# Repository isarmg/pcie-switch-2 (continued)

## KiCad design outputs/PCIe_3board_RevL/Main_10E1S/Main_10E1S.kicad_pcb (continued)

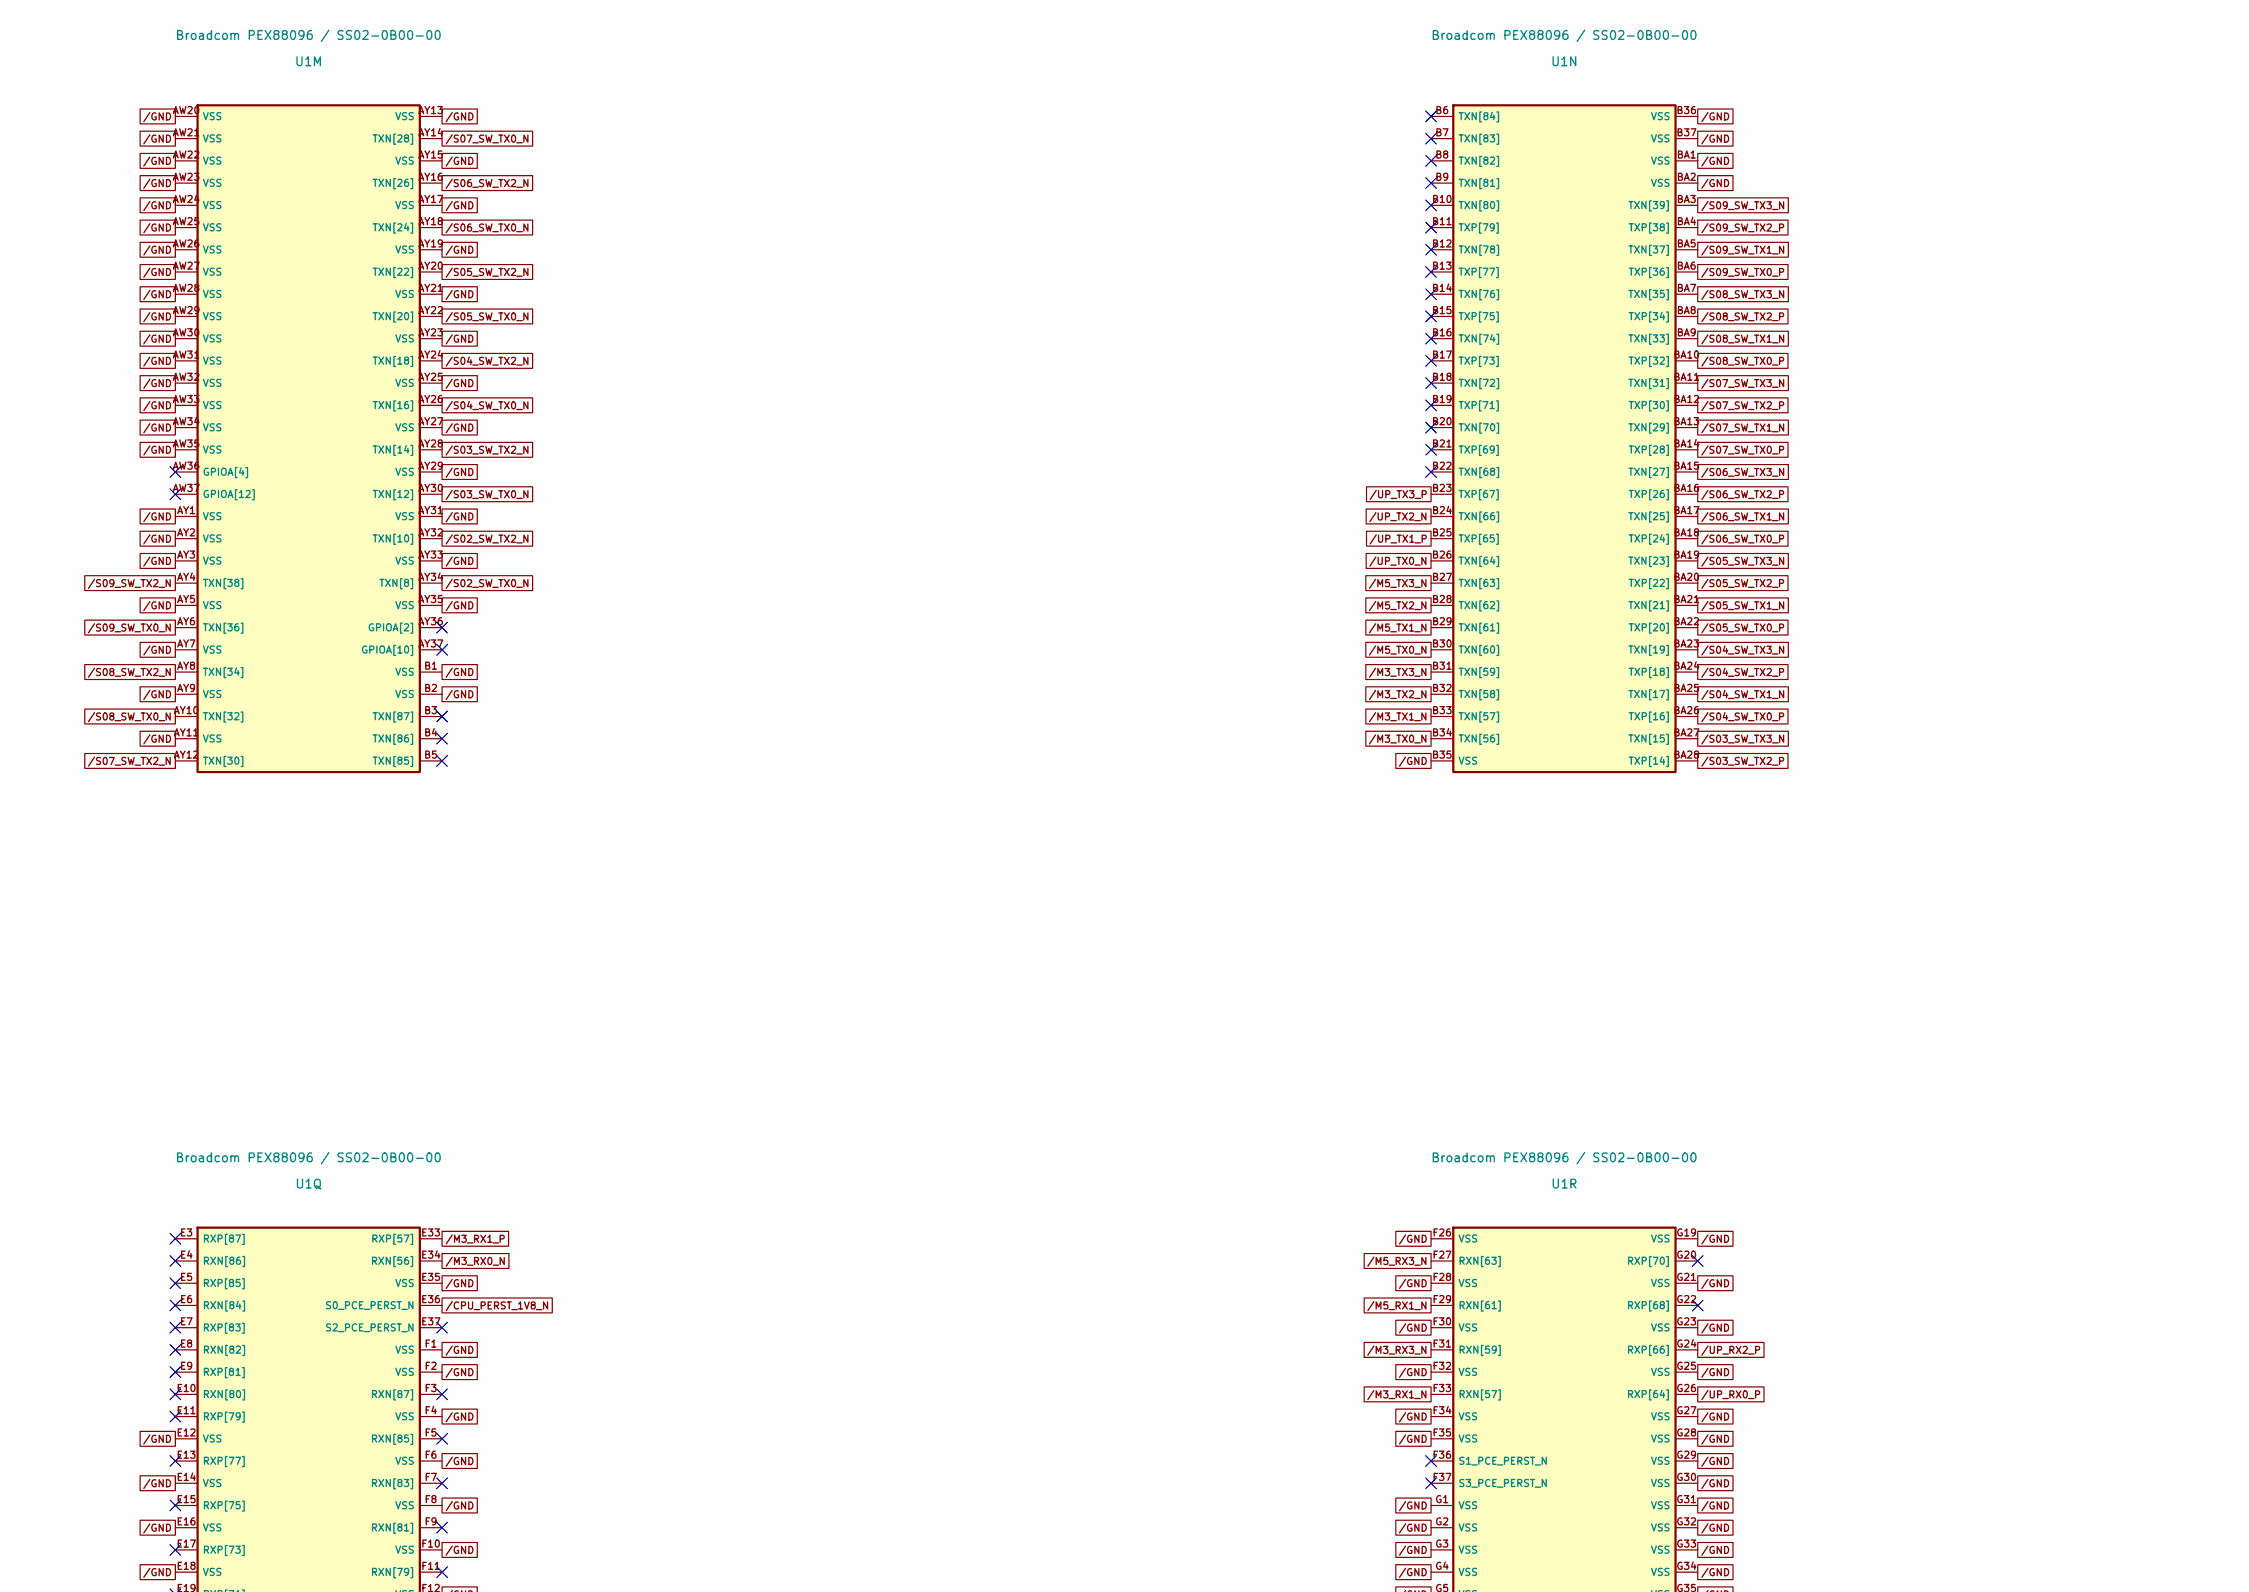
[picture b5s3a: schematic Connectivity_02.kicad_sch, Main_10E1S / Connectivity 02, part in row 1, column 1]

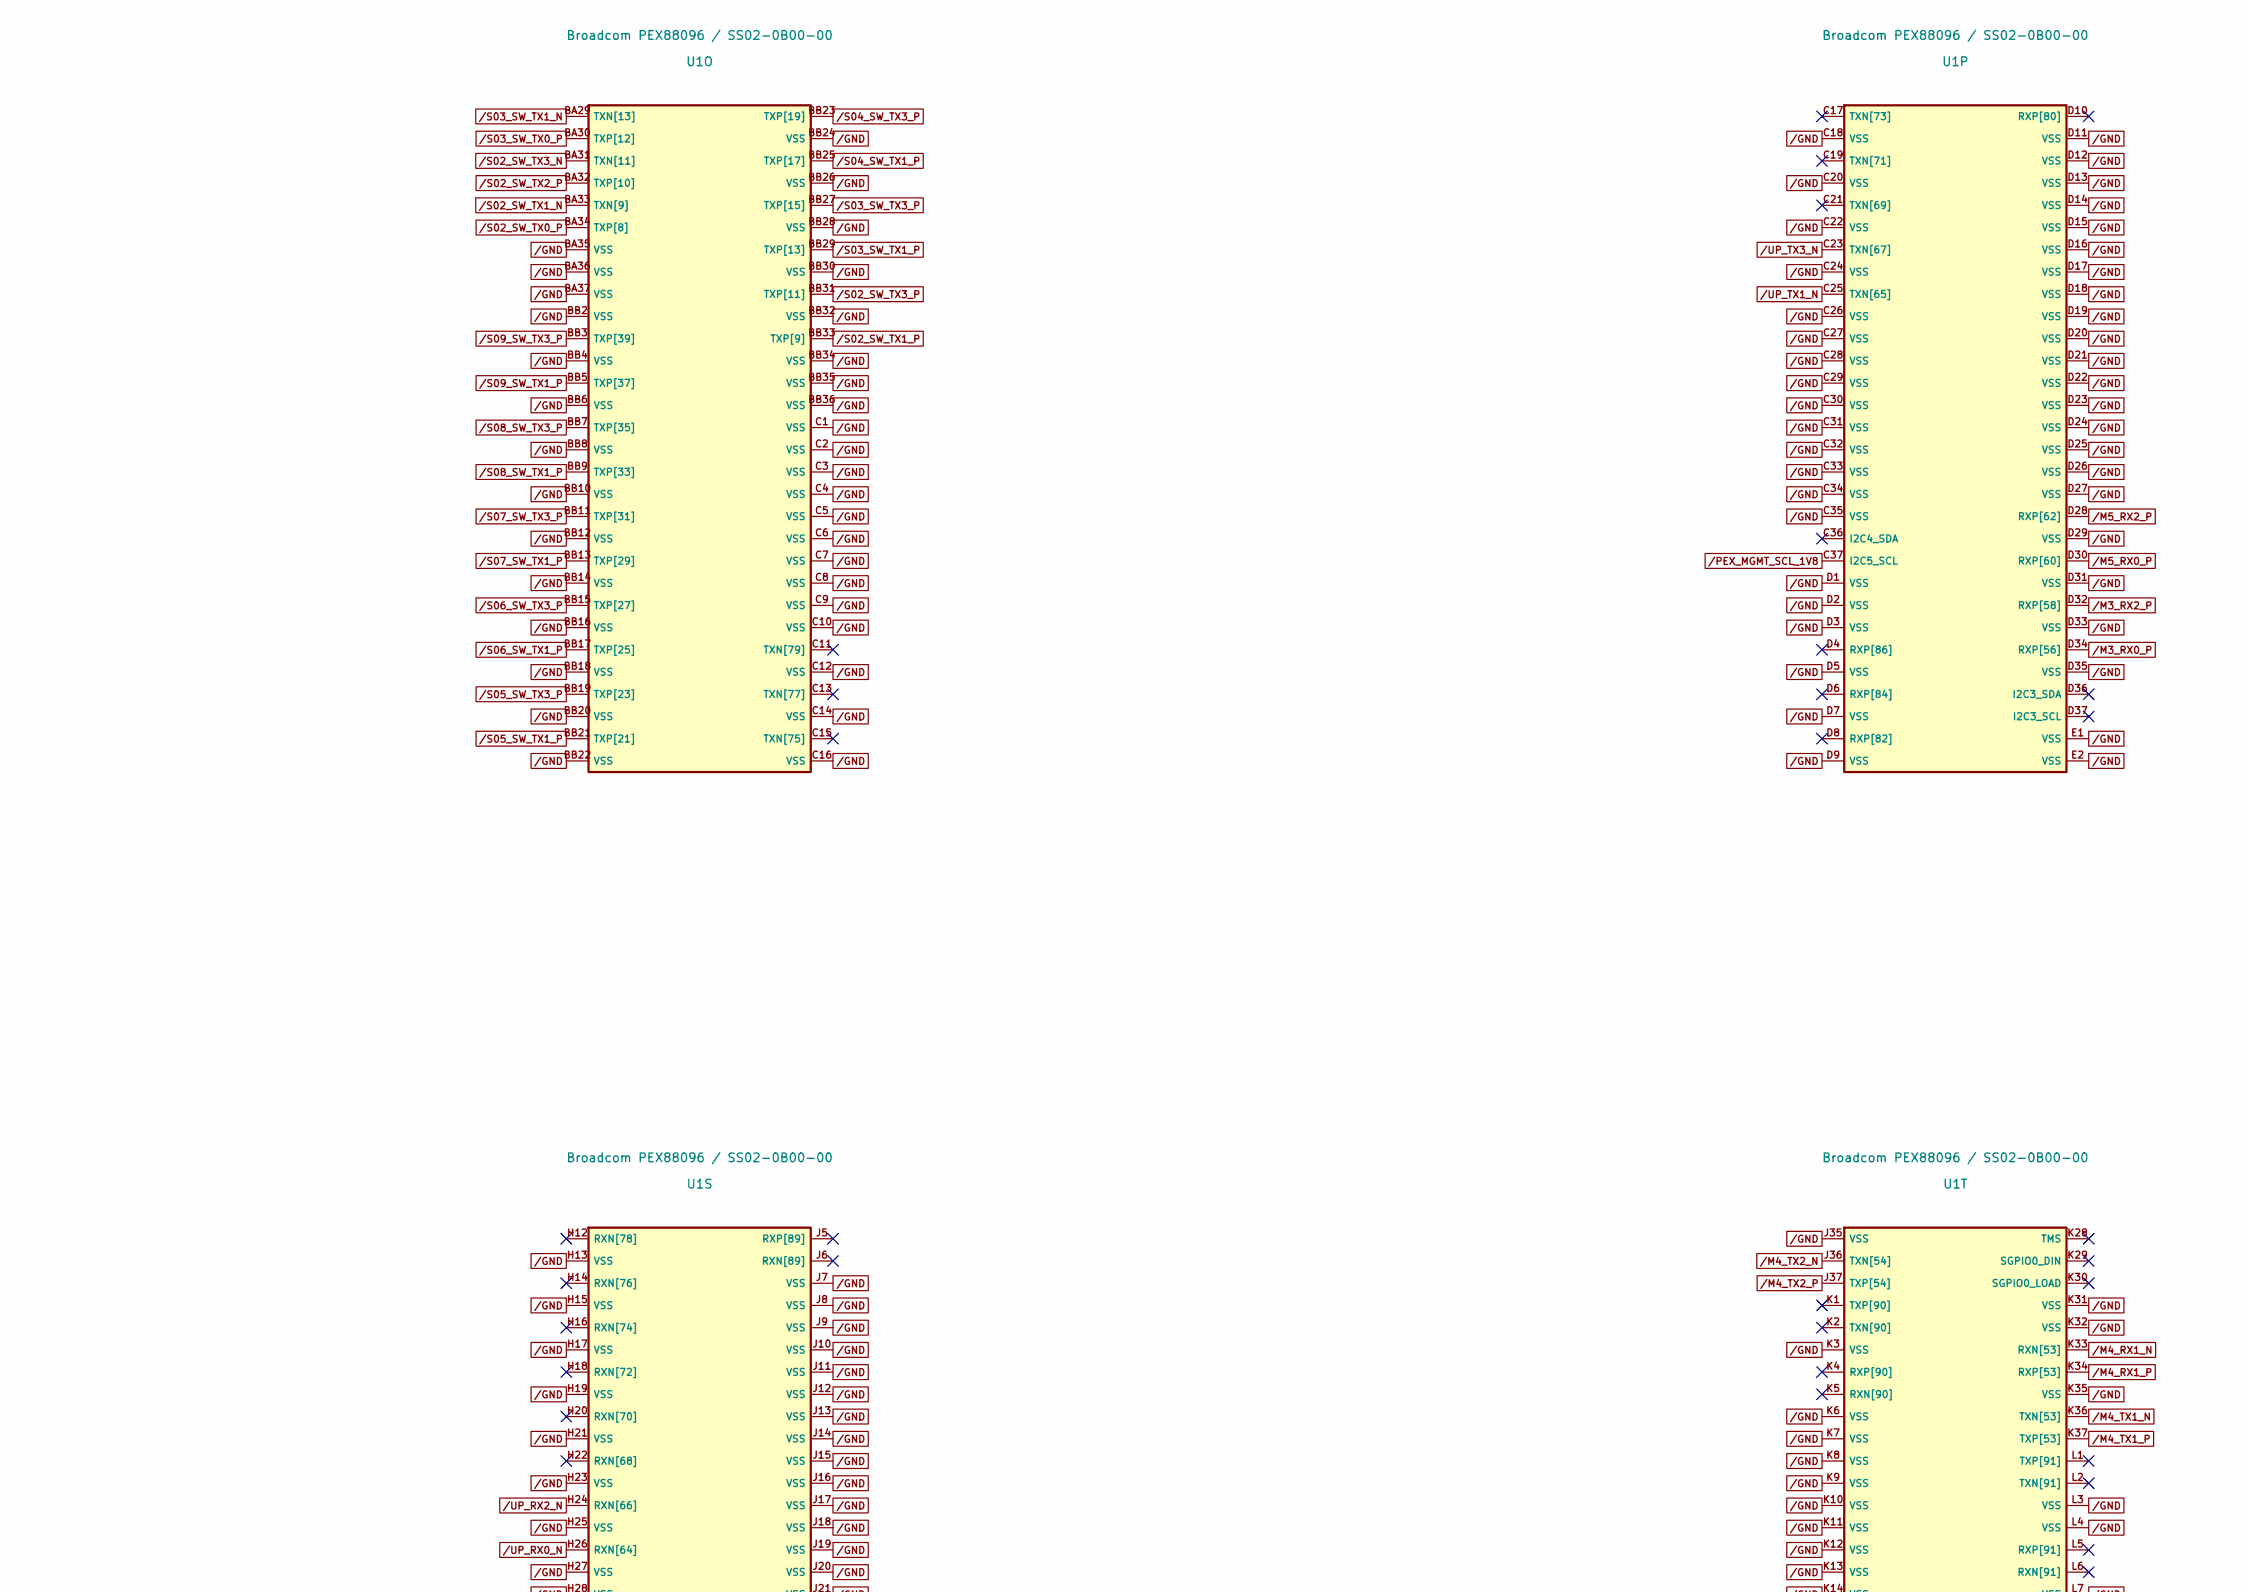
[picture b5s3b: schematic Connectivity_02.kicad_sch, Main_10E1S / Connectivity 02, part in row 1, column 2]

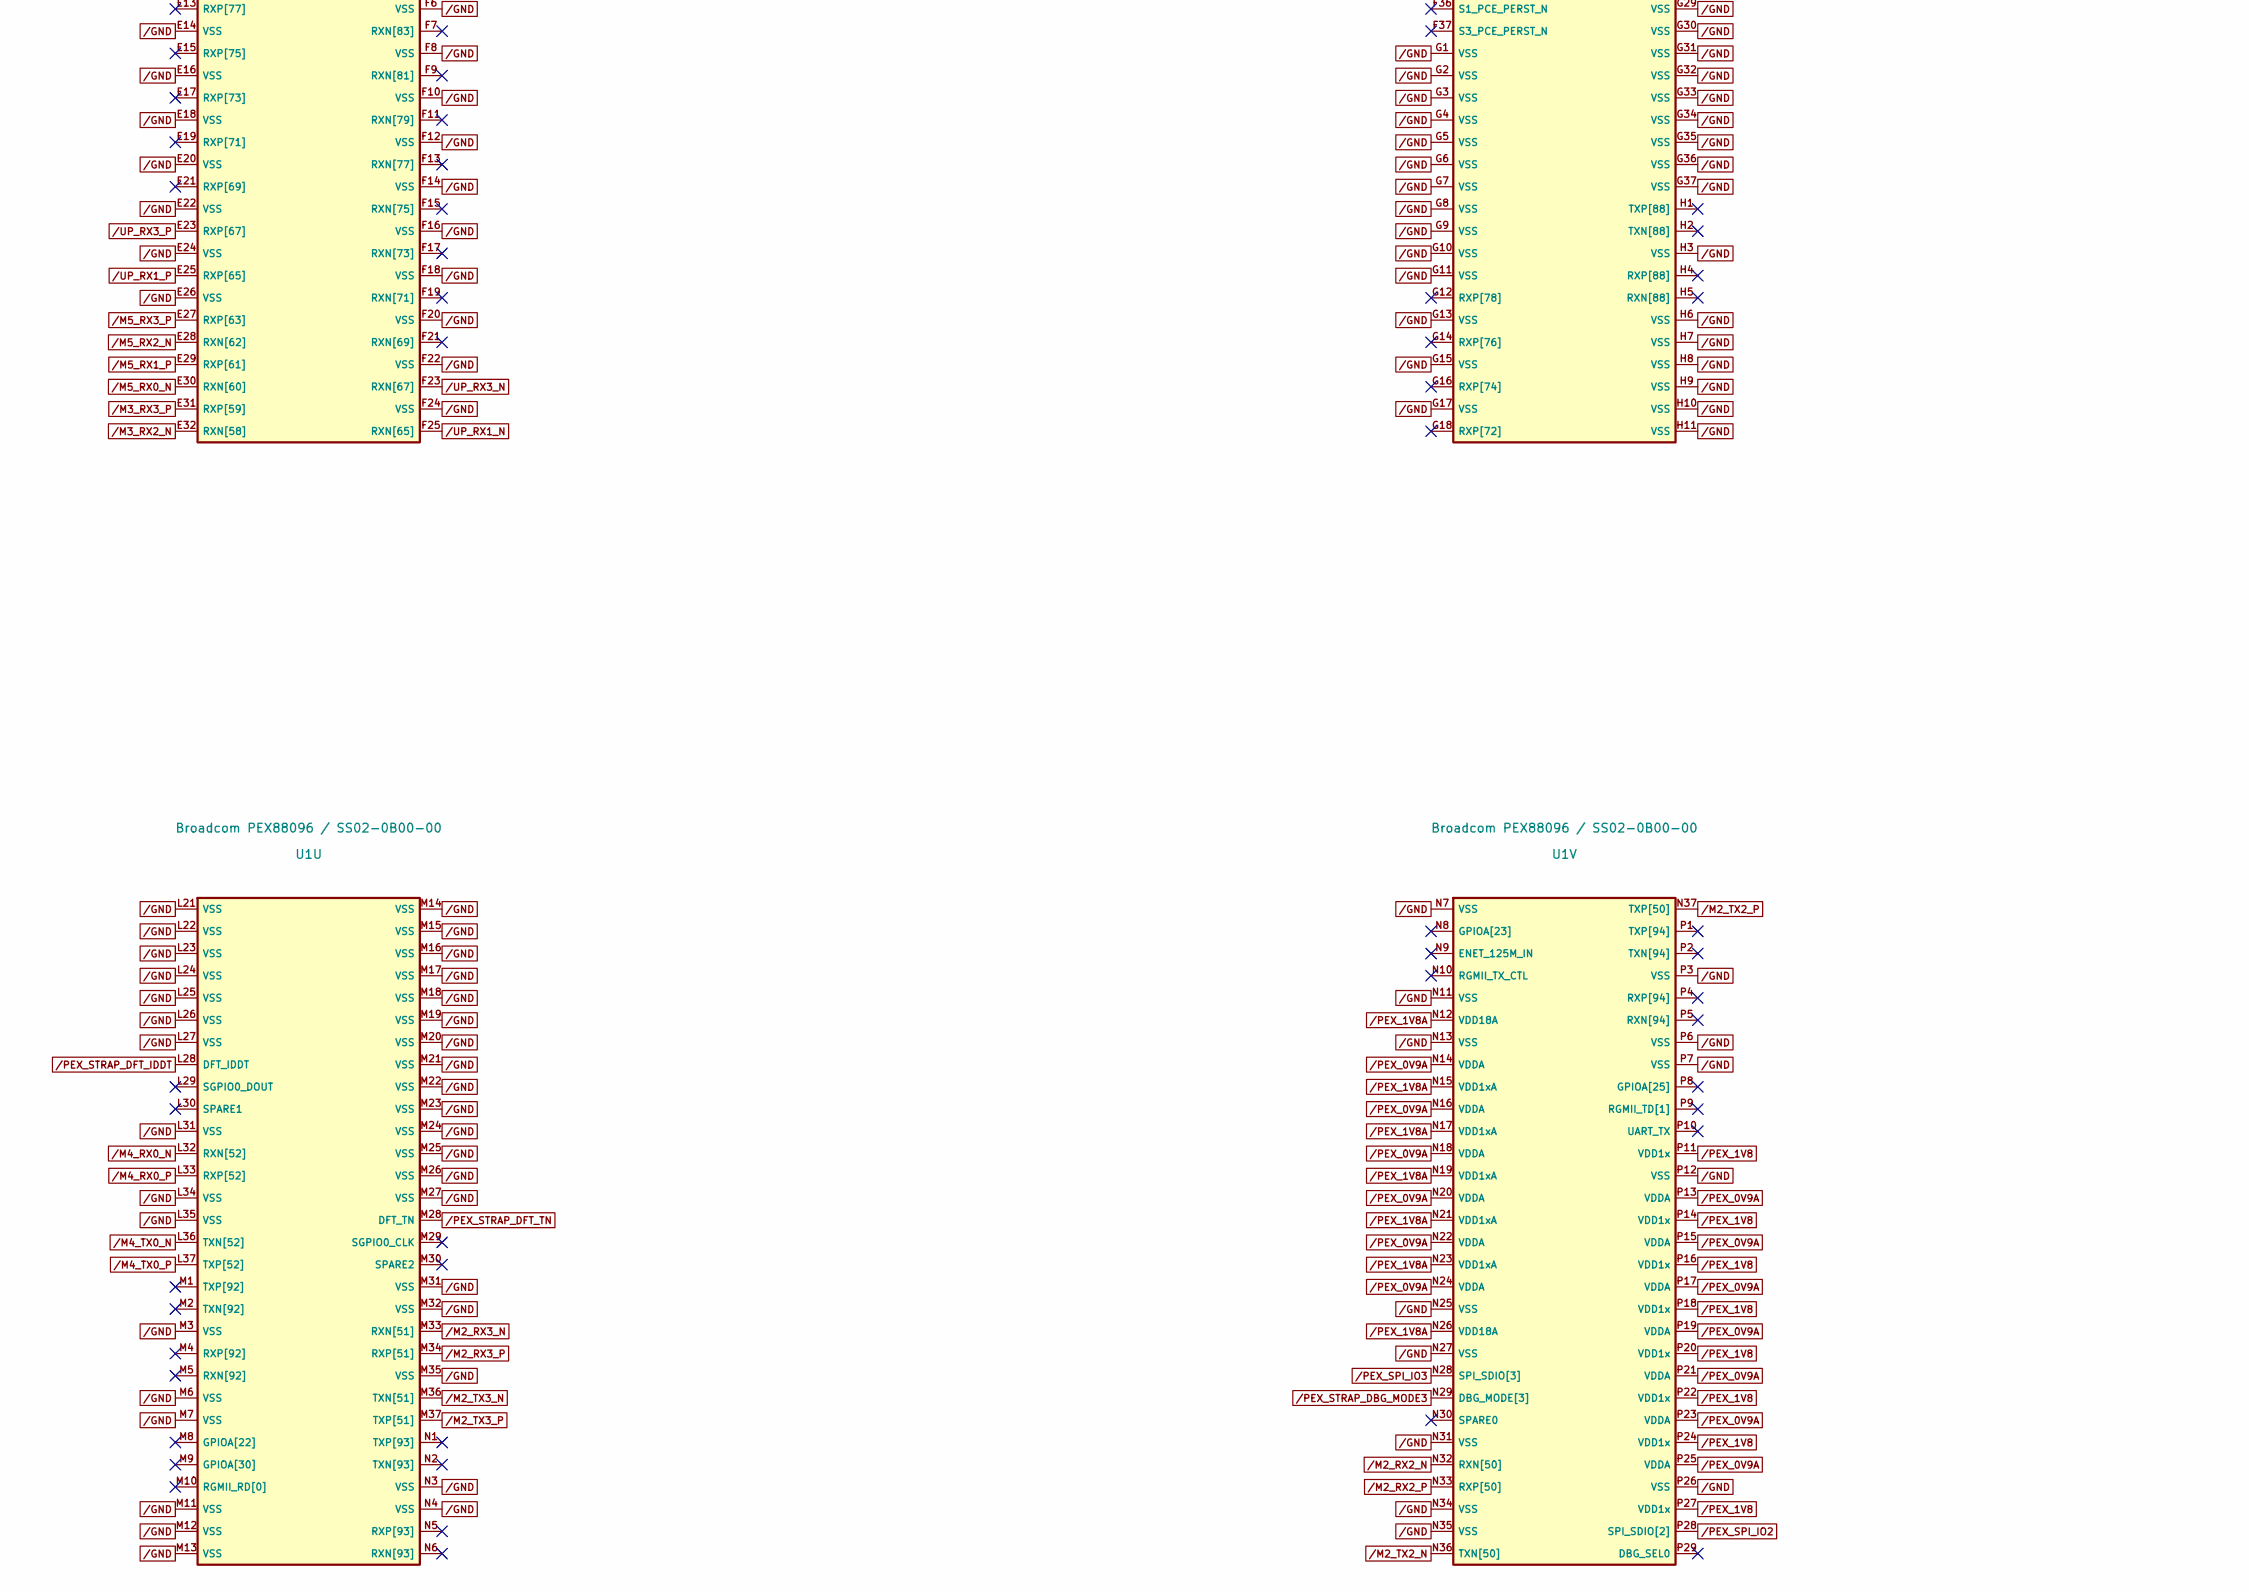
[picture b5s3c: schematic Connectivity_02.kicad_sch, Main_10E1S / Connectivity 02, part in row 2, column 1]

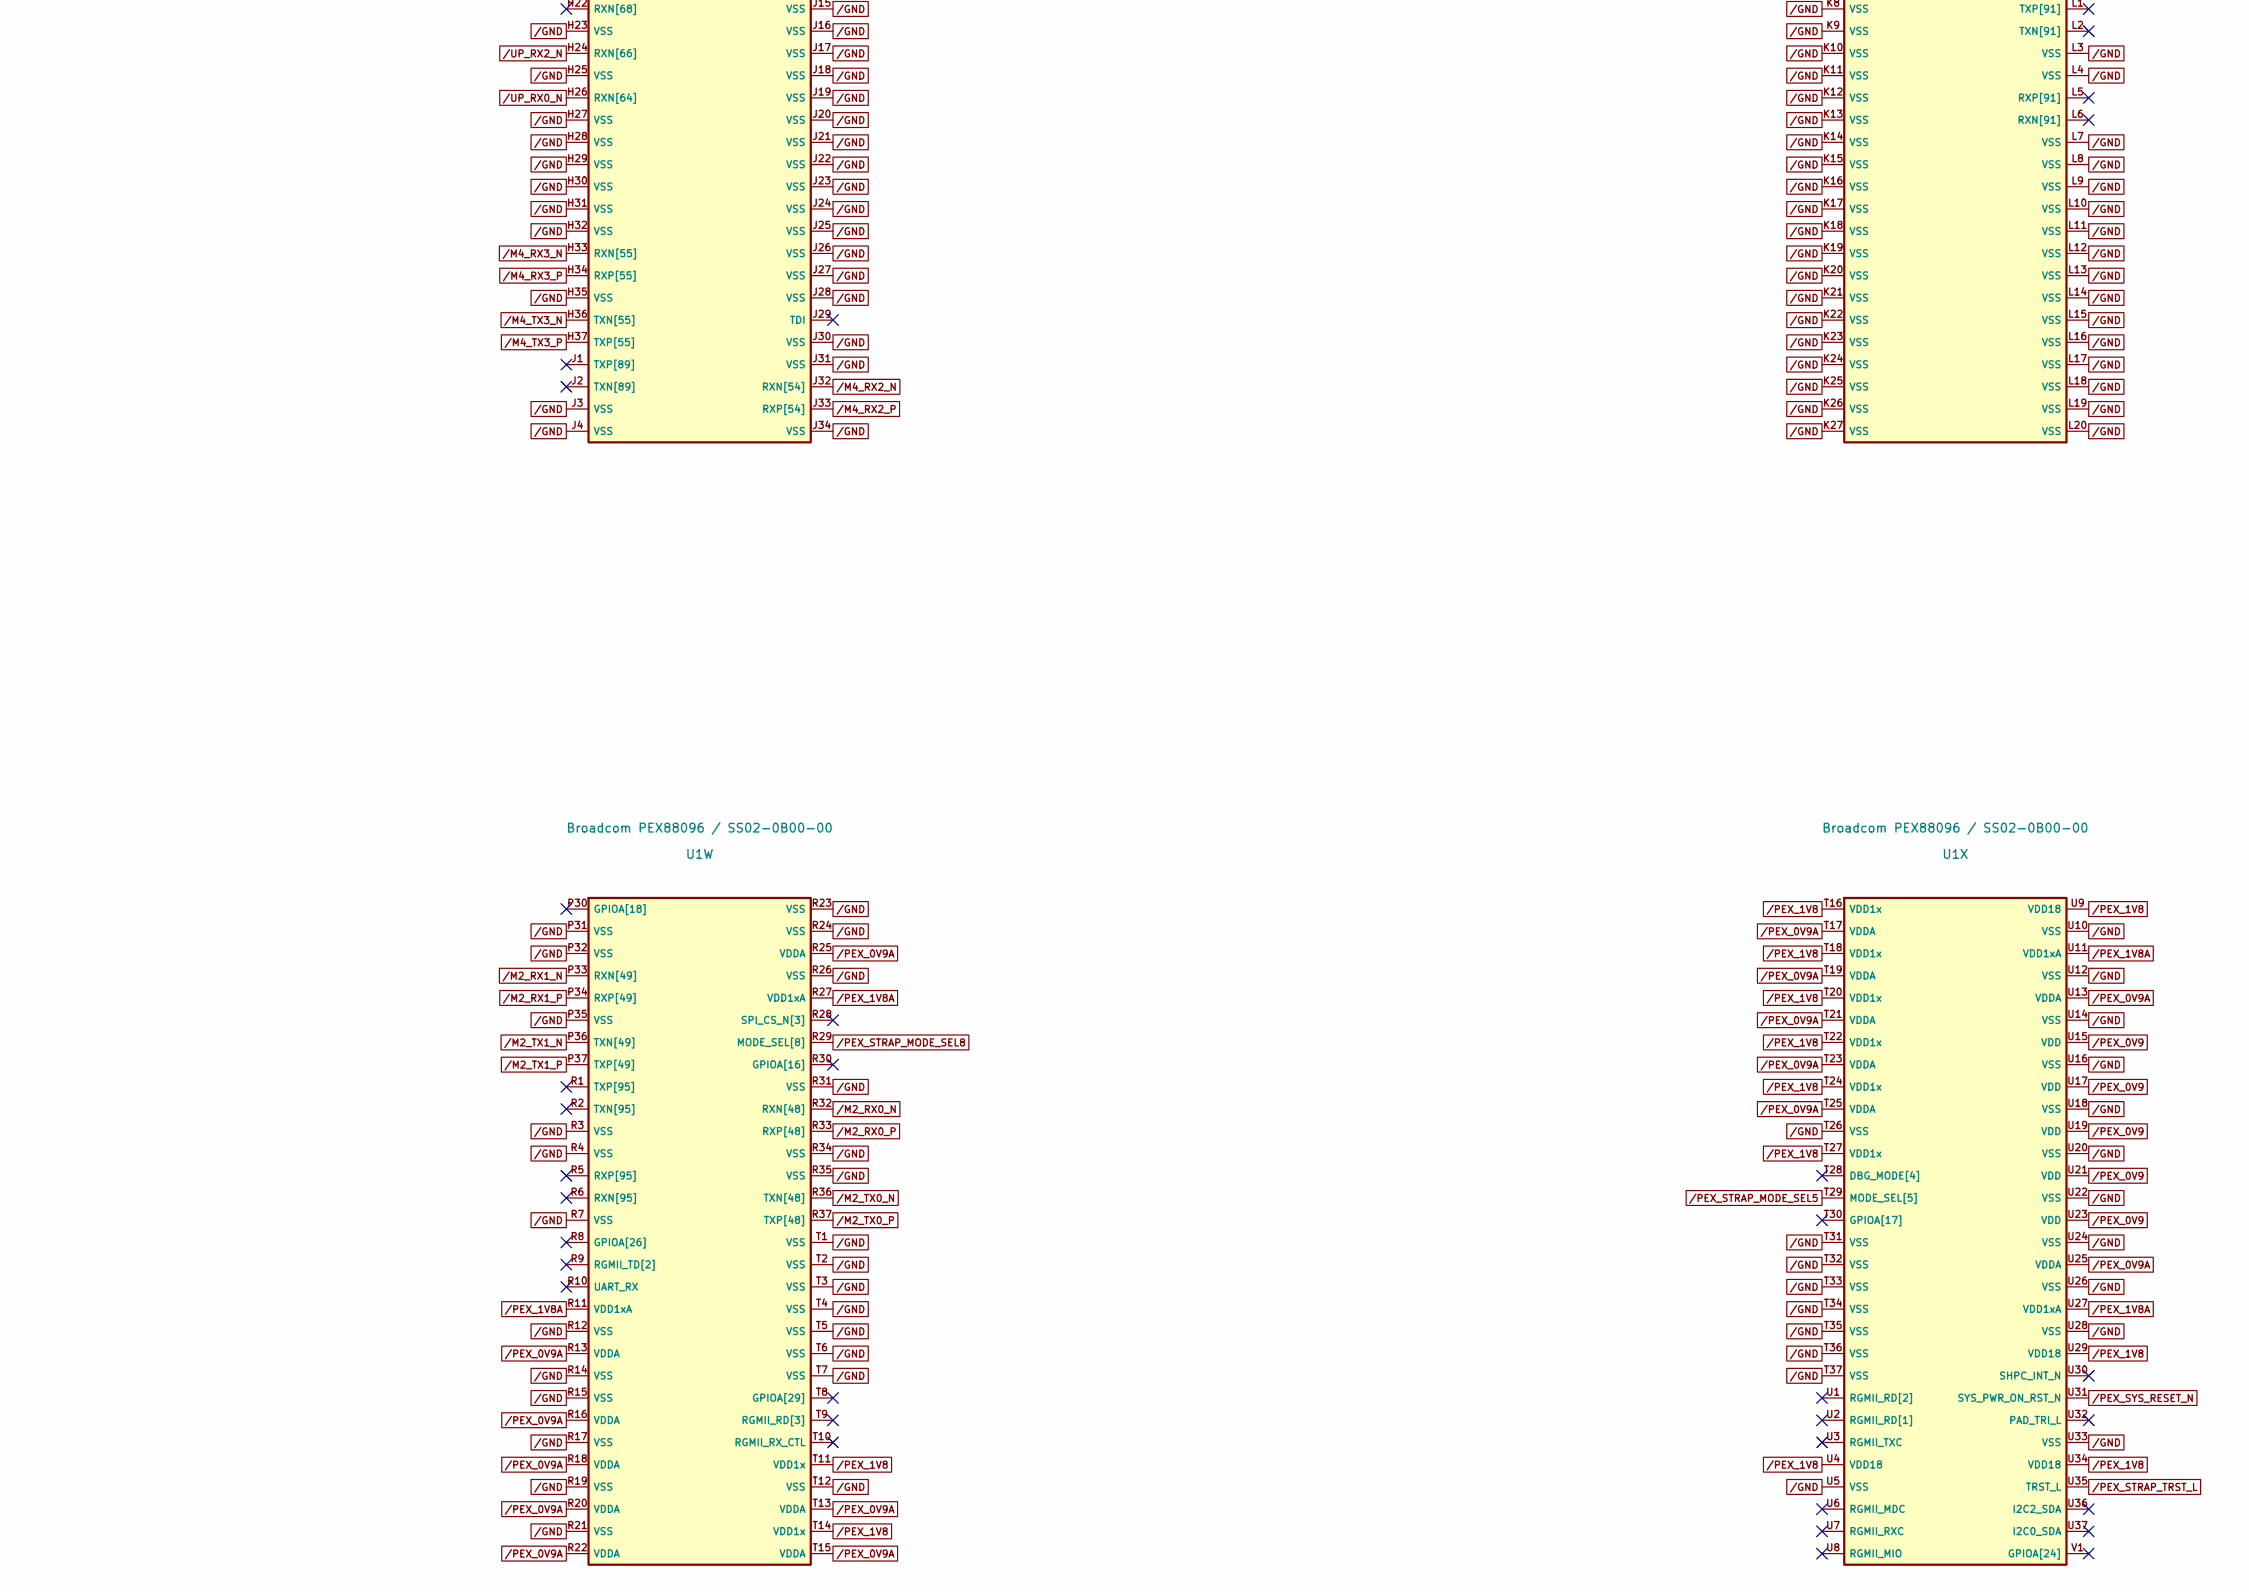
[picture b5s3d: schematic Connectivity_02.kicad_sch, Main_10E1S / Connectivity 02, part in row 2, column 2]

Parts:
U1: Broadcom PEX88096 / SS02-0B00-00; Broadcom_PEX88096_BGA1550_37p5x42p5_1mm

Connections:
/CPU_PERST_1V8_N: U1.E36 (S0_PCE_PERST_N); also elsewhere on the board
/GND: U1.AW20 (VSS), U1.AW21 (VSS), U1.AW22 (VSS), U1.AW23 (VSS), U1.AW24 (VSS), U1.AW25 (VSS), U1.AW26 (VSS), U1.AW27 (VSS), U1.AW28 (VSS), U1.AW29 (VSS), U1.AW30 (VSS), U1.AW31 (VSS), U1.AW32 (VSS), U1.AW33 (VSS), U1.AW34 (VSS), U1.AW35 (VSS), U1.AY1 (VSS), U1.AY2 (VSS), U1.AY3 (VSS), U1.AY5 (VSS), U1.AY7 (VSS), U1.AY9 (VSS), U1.AY11 (VSS), U1.AY13 (VSS), U1.AY15 (VSS), U1.AY17 (VSS), U1.AY19 (VSS), U1.AY21 (VSS), U1.AY23 (VSS), U1.AY25 (VSS), U1.AY27 (VSS), U1.AY29 (VSS), U1.AY31 (VSS), U1.AY33 (VSS), U1.AY35 (VSS), U1.B1 (VSS), U1.B2 (VSS), U1.B35 (VSS), U1.B36 (VSS), U1.B37 (VSS), U1.BA1 (VSS), U1.BA2 (VSS), U1.BA35 (VSS), U1.BA36 (VSS), U1.BA37 (VSS), U1.BB2 (VSS), U1.BB4 (VSS), U1.BB6 (VSS), U1.BB8 (VSS), U1.BB10 (VSS), U1.BB12 (VSS), U1.BB14 (VSS), U1.BB16 (VSS), U1.BB18 (VSS), U1.BB20 (VSS), U1.BB22 (VSS), U1.BB24 (VSS), U1.BB26 (VSS), U1.BB28 (VSS), U1.BB30 (VSS), U1.BB32 (VSS), U1.BB34 (VSS), U1.BB35 (VSS), U1.BB36 (VSS), U1.C1 (VSS), U1.C2 (VSS), U1.C3 (VSS), U1.C4 (VSS), U1.C5 (VSS), U1.C6 (VSS), U1.C7 (VSS), U1.C8 (VSS), U1.C9 (VSS), U1.C10 (VSS), U1.C12 (VSS), U1.C14 (VSS), U1.C16 (VSS), U1.C18 (VSS), U1.C20 (VSS), U1.C22 (VSS), U1.C24 (VSS), U1.C26 (VSS), U1.C27 (VSS), U1.C28 (VSS), U1.C29 (VSS), U1.C30 (VSS), U1.C31 (VSS), U1.C32 (VSS), U1.C33 (VSS), U1.C34 (VSS), U1.C35 (VSS), U1.D1 (VSS), U1.D2 (VSS), U1.D3 (VSS), U1.D5 (VSS), U1.D7 (VSS), U1.D9 (VSS), U1.D11 (VSS), U1.D12 (VSS), U1.D13 (VSS), U1.D14 (VSS), U1.D15 (VSS), U1.D16 (VSS), U1.D17 (VSS), U1.D18 (VSS), U1.D19 (VSS), U1.D20 (VSS), U1.D21 (VSS), U1.D22 (VSS), U1.D23 (VSS), U1.D24 (VSS), U1.D25 (VSS), U1.D26 (VSS), U1.D27 (VSS), U1.D29 (VSS), U1.D31 (VSS), U1.D33 (VSS), U1.D35 (VSS), U1.E1 (VSS), U1.E2 (VSS), U1.E12 (VSS), U1.E14 (VSS), U1.E16 (VSS), U1.E18 (VSS), U1.E20 (VSS), U1.E22 (VSS), U1.E24 (VSS), U1.E26 (VSS), U1.E35 (VSS), U1.F1 (VSS), U1.F2 (VSS), U1.F4 (VSS), U1.F6 (VSS), U1.F8 (VSS), U1.F10 (VSS), U1.F12 (VSS), U1.F14 (VSS), U1.F16 (VSS), U1.F18 (VSS), U1.F20 (VSS), U1.F22 (VSS), U1.F24 (VSS), U1.F26 (VSS), U1.F28 (VSS), U1.F30 (VSS), U1.F32 (VSS), U1.F34 (VSS), U1.F35 (VSS), U1.G1 (VSS), U1.G2 (VSS), U1.G3 (VSS), U1.G4 (VSS), U1.G5 (VSS), U1.G6 (VSS), U1.G7 (VSS), U1.G8 (VSS), U1.G9 (VSS), U1.G10 (VSS), U1.G11 (VSS), U1.G13 (VSS), U1.G15 (VSS), U1.G17 (VSS), U1.G19 (VSS), U1.G21 (VSS), U1.G23 (VSS), U1.G25 (VSS), U1.G27 (VSS), U1.G28 (VSS), U1.G29 (VSS), U1.G30 (VSS), U1.G31 (VSS), U1.G32 (VSS), U1.G33 (VSS), U1.G34 (VSS), U1.G35 (VSS), U1.G36 (VSS), U1.G37 (VSS), U1.H3 (VSS), U1.H6 (VSS), U1.H7 (VSS), U1.H8 (VSS), U1.H9 (VSS), U1.H10 (VSS), U1.H11 (VSS), U1.H13 (VSS), U1.H15 (VSS), U1.H17 (VSS), U1.H19 (VSS), U1.H21 (VSS), U1.H23 (VSS), U1.H25 (VSS), U1.H27 (VSS), U1.H28 (VSS), U1.H29 (VSS), U1.H30 (VSS), U1.H31 (VSS), U1.H32 (VSS), U1.H35 (VSS), U1.J3 (VSS), U1.J4 (VSS), U1.J7 (VSS), U1.J8 (VSS), U1.J9 (VSS), U1.J10 (VSS), U1.J11 (VSS), U1.J12 (VSS), U1.J13 (VSS), U1.J14 (VSS), U1.J15 (VSS), U1.J16 (VSS), U1.J17 (VSS), U1.J18 (VSS), U1.J19 (VSS), U1.J20 (VSS), U1.J21 (VSS), U1.J22 (VSS), U1.J23 (VSS), U1.J24 (VSS), U1.J25 (VSS), U1.J26 (VSS), U1.J27 (VSS), U1.J28 (VSS), U1.J30 (VSS), U1.J31 (VSS), U1.J34 (VSS), U1.J35 (VSS), U1.K3 (VSS), U1.K6 (VSS), U1.K7 (VSS), U1.K8 (VSS), U1.K9 (VSS), U1.K10 (VSS), U1.K11 (VSS), U1.K12 (VSS), U1.K13 (VSS), U1.K14 (VSS), U1.K15 (VSS), U1.K16 (VSS), U1.K17 (VSS), U1.K18 (VSS), U1.K19 (VSS), U1.K20 (VSS), U1.K21 (VSS), U1.K22 (VSS), U1.K23 (VSS), U1.K24 (VSS), U1.K25 (VSS), U1.K26 (VSS), U1.K27 (VSS), U1.K31 (VSS), U1.K32 (VSS), U1.K35 (VSS), U1.L3 (VSS), U1.L4 (VSS), U1.L7 (VSS), U1.L8 (VSS), U1.L9 (VSS), U1.L10 (VSS), U1.L11 (VSS), U1.L12 (VSS), U1.L13 (VSS), U1.L14 (VSS), U1.L15 (VSS), U1.L16 (VSS), U1.L17 (VSS), U1.L18 (VSS), U1.L19 (VSS), U1.L20 (VSS), U1.L21 (VSS), U1.L22 (VSS), U1.L23 (VSS), U1.L24 (VSS), U1.L25 (VSS), U1.L26 (VSS), U1.L27 (VSS), U1.L31 (VSS), U1.L34 (VSS), U1.L35 (VSS), U1.M3 (VSS), U1.M6 (VSS), U1.M7 (VSS), U1.M11 (VSS), U1.M12 (VSS), U1.M13 (VSS), U1.M14 (VSS), U1.M15 (VSS), U1.M16 (VSS), U1.M17 (VSS), U1.M18 (VSS), U1.M19 (VSS), U1.M20 (VSS), U1.M21 (VSS), U1.M22 (VSS), U1.M23 (VSS), U1.M24 (VSS), U1.M25 (VSS), U1.M26 (VSS), U1.M27 (VSS), U1.M31 (VSS), U1.M32 (VSS), U1.M35 (VSS), U1.N3 (VSS), U1.N4 (VSS), U1.N7 (VSS), U1.N11 (VSS), U1.N13 (VSS), U1.N25 (VSS), U1.N27 (VSS), U1.N31 (VSS), U1.N34 (VSS), U1.N35 (VSS), U1.P3 (VSS), U1.P6 (VSS), U1.P7 (VSS), U1.P12 (VSS), U1.P26 (VSS), U1.P31 (VSS), U1.P32 (VSS), U1.P35 (VSS), U1.R3 (VSS), U1.R4 (VSS), U1.R7 (VSS), U1.R12 (VSS), U1.R14 (VSS), U1.R15 (VSS), U1.R17 (VSS), U1.R19 (VSS), U1.R21 (VSS), U1.R23 (VSS), U1.R24 (VSS), U1.R26 (VSS), U1.R31 (VSS), U1.R34 (VSS), U1.R35 (VSS), U1.T1 (VSS), U1.T2 (VSS), U1.T3 (VSS), U1.T4 (VSS), U1.T5 (VSS), U1.T6 (VSS), U1.T7 (VSS), U1.T12 (VSS), U1.T26 (VSS), U1.T31 (VSS), U1.T32 (VSS), U1.T33 (VSS), U1.T34 (VSS), U1.T35 (VSS), U1.T36 (VSS), U1.T37 (VSS), U1.U5 (VSS), U1.U10 (VSS), U1.U12 (VSS), U1.U14 (VSS), U1.U16 (VSS), U1.U18 (VSS), U1.U20 (VSS), U1.U22 (VSS), U1.U24 (VSS), U1.U26 (VSS), U1.U28 (VSS), U1.U33 (VSS); also elsewhere on the board
/M2_RX0_N: U1.R32 (RXN[48]); also elsewhere on the board
/M2_RX0_P: U1.R33 (RXP[48]); also elsewhere on the board
/M2_RX1_N: U1.P33 (RXN[49]); also elsewhere on the board
/M2_RX1_P: U1.P34 (RXP[49]); also elsewhere on the board
/M2_RX2_N: U1.N32 (RXN[50]); also elsewhere on the board
/M2_RX2_P: U1.N33 (RXP[50]); also elsewhere on the board
/M2_RX3_N: U1.M33 (RXN[51]); also elsewhere on the board
/M2_RX3_P: U1.M34 (RXP[51]); also elsewhere on the board
/M2_TX0_N: U1.R36 (TXN[48]); also elsewhere on the board
/M2_TX0_P: U1.R37 (TXP[48]); also elsewhere on the board
/M2_TX1_N: U1.P36 (TXN[49]); also elsewhere on the board
/M2_TX1_P: U1.P37 (TXP[49]); also elsewhere on the board
/M2_TX2_N: U1.N36 (TXN[50]); also elsewhere on the board
/M2_TX2_P: U1.N37 (TXP[50]); also elsewhere on the board
/M2_TX3_N: U1.M36 (TXN[51]); also elsewhere on the board
/M2_TX3_P: U1.M37 (TXP[51]); also elsewhere on the board
/M3_RX0_N: U1.E34 (RXN[56]); also elsewhere on the board
/M3_RX0_P: U1.D34 (RXP[56]); also elsewhere on the board
/M3_RX1_N: U1.F33 (RXN[57]); also elsewhere on the board
/M3_RX1_P: U1.E33 (RXP[57]); also elsewhere on the board
/M3_RX2_N: U1.E32 (RXN[58]); also elsewhere on the board
/M3_RX2_P: U1.D32 (RXP[58]); also elsewhere on the board
/M3_RX3_N: U1.F31 (RXN[59]); also elsewhere on the board
/M3_RX3_P: U1.E31 (RXP[59]); also elsewhere on the board
/M3_TX0_N: U1.B34 (TXN[56]); also elsewhere on the board
/M3_TX1_N: U1.B33 (TXN[57]); also elsewhere on the board
/M3_TX2_N: U1.B32 (TXN[58]); also elsewhere on the board
/M3_TX3_N: U1.B31 (TXN[59]); also elsewhere on the board
/M4_RX0_N: U1.L32 (RXN[52]); also elsewhere on the board
/M4_RX0_P: U1.L33 (RXP[52]); also elsewhere on the board
/M4_RX1_N: U1.K33 (RXN[53]); also elsewhere on the board
/M4_RX1_P: U1.K34 (RXP[53]); also elsewhere on the board
/M4_RX2_N: U1.J32 (RXN[54]); also elsewhere on the board
/M4_RX2_P: U1.J33 (RXP[54]); also elsewhere on the board
/M4_RX3_N: U1.H33 (RXN[55]); also elsewhere on the board
/M4_RX3_P: U1.H34 (RXP[55]); also elsewhere on the board
/M4_TX0_N: U1.L36 (TXN[52]); also elsewhere on the board
/M4_TX0_P: U1.L37 (TXP[52]); also elsewhere on the board
/M4_TX1_N: U1.K36 (TXN[53]); also elsewhere on the board
/M4_TX1_P: U1.K37 (TXP[53]); also elsewhere on the board
/M4_TX2_N: U1.J36 (TXN[54]); also elsewhere on the board
/M4_TX2_P: U1.J37 (TXP[54]); also elsewhere on the board
/M4_TX3_N: U1.H36 (TXN[55]); also elsewhere on the board
/M4_TX3_P: U1.H37 (TXP[55]); also elsewhere on the board
/M5_RX0_N: U1.E30 (RXN[60]); also elsewhere on the board
/M5_RX0_P: U1.D30 (RXP[60]); also elsewhere on the board
/M5_RX1_N: U1.F29 (RXN[61]); also elsewhere on the board
/M5_RX1_P: U1.E29 (RXP[61]); also elsewhere on the board
/M5_RX2_N: U1.E28 (RXN[62]); also elsewhere on the board
/M5_RX2_P: U1.D28 (RXP[62]); also elsewhere on the board
/M5_RX3_N: U1.F27 (RXN[63]); also elsewhere on the board
/M5_RX3_P: U1.E27 (RXP[63]); also elsewhere on the board
/M5_TX0_N: U1.B30 (TXN[60]); also elsewhere on the board
/M5_TX1_N: U1.B29 (TXN[61]); also elsewhere on the board
/M5_TX2_N: U1.B28 (TXN[62]); also elsewhere on the board
/M5_TX3_N: U1.B27 (TXN[63]); also elsewhere on the board
/PEX_0V9: U1.U15 (VDD), U1.U17 (VDD), U1.U19 (VDD), U1.U21 (VDD), U1.U23 (VDD); also elsewhere on the board
/PEX_0V9A: U1.N14 (VDDA), U1.N16 (VDDA), U1.N18 (VDDA), U1.N20 (VDDA), U1.N22 (VDDA), U1.N24 (VDDA), U1.P13 (VDDA), U1.P15 (VDDA), U1.P17 (VDDA), U1.P19 (VDDA), U1.P21 (VDDA), U1.P23 (VDDA), U1.P25 (VDDA), U1.R13 (VDDA), U1.R16 (VDDA), U1.R18 (VDDA), U1.R20 (VDDA), U1.R22 (VDDA), U1.R25 (VDDA), U1.T13 (VDDA), U1.T15 (VDDA), U1.T17 (VDDA), U1.T19 (VDDA), U1.T21 (VDDA), U1.T23 (VDDA), U1.T25 (VDDA), U1.U13 (VDDA), U1.U25 (VDDA); also elsewhere on the board
/PEX_1V8: U1.P11 (VDD1x), U1.P14 (VDD1x), U1.P16 (VDD1x), U1.P18 (VDD1x), U1.P20 (VDD1x), U1.P22 (VDD1x), U1.P24 (VDD1x), U1.P27 (VDD1x), U1.T11 (VDD1x), U1.T14 (VDD1x), U1.T16 (VDD1x), U1.T18 (VDD1x), U1.T20 (VDD1x), U1.T22 (VDD1x), U1.T24 (VDD1x), U1.T27 (VDD1x), U1.U4 (VDD18), U1.U9 (VDD18), U1.U29 (VDD18), U1.U34 (VDD18); also elsewhere on the board
/PEX_1V8A: U1.N12 (VDD18A), U1.N15 (VDD1xA), U1.N17 (VDD1xA), U1.N19 (VDD1xA), U1.N21 (VDD1xA), U1.N23 (VDD1xA), U1.N26 (VDD18A), U1.R11 (VDD1xA), U1.R27 (VDD1xA), U1.U11 (VDD1xA), U1.U27 (VDD1xA); also elsewhere on the board
/PEX_MGMT_SCL_1V8: U1.C37 (I2C5_SCL)
/PEX_SPI_IO2: U1.P28 (SPI_SDIO[2]); also elsewhere on the board
/PEX_SPI_IO3: U1.N28 (SPI_SDIO[3]); also elsewhere on the board
/PEX_STRAP_DBG_MODE3: U1.N29 (DBG_MODE[3])
/PEX_STRAP_DFT_IDDT: U1.L28 (DFT_IDDT)
/PEX_STRAP_DFT_TN: U1.M28 (DFT_TN)
/PEX_STRAP_MODE_SEL5: U1.T29 (MODE_SEL[5])
/PEX_STRAP_MODE_SEL8: U1.R29 (MODE_SEL[8])
/PEX_STRAP_TRST_L: U1.U35 (TRST_L)
/PEX_SYS_RESET_N: U1.U31 (SYS_PWR_ON_RST_N); also elsewhere on the board
/S02_SW_TX0_N: U1.AY34 (TXN[8]); also elsewhere on the board
/S02_SW_TX0_P: U1.BA34 (TXP[8]); also elsewhere on the board
/S02_SW_TX1_N: U1.BA33 (TXN[9]); also elsewhere on the board
/S02_SW_TX1_P: U1.BB33 (TXP[9]); also elsewhere on the board
/S02_SW_TX2_N: U1.AY32 (TXN[10]); also elsewhere on the board
/S02_SW_TX2_P: U1.BA32 (TXP[10]); also elsewhere on the board
/S02_SW_TX3_N: U1.BA31 (TXN[11]); also elsewhere on the board
/S02_SW_TX3_P: U1.BB31 (TXP[11]); also elsewhere on the board
/S03_SW_TX0_N: U1.AY30 (TXN[12]); also elsewhere on the board
/S03_SW_TX0_P: U1.BA30 (TXP[12]); also elsewhere on the board
/S03_SW_TX1_N: U1.BA29 (TXN[13]); also elsewhere on the board
/S03_SW_TX1_P: U1.BB29 (TXP[13]); also elsewhere on the board
/S03_SW_TX2_N: U1.AY28 (TXN[14]); also elsewhere on the board
/S03_SW_TX2_P: U1.BA28 (TXP[14]); also elsewhere on the board
/S03_SW_TX3_N: U1.BA27 (TXN[15]); also elsewhere on the board
/S03_SW_TX3_P: U1.BB27 (TXP[15]); also elsewhere on the board
/S04_SW_TX0_N: U1.AY26 (TXN[16]); also elsewhere on the board
/S04_SW_TX0_P: U1.BA26 (TXP[16]); also elsewhere on the board
/S04_SW_TX1_N: U1.BA25 (TXN[17]); also elsewhere on the board
/S04_SW_TX1_P: U1.BB25 (TXP[17]); also elsewhere on the board
/S04_SW_TX2_N: U1.AY24 (TXN[18]); also elsewhere on the board
/S04_SW_TX2_P: U1.BA24 (TXP[18]); also elsewhere on the board
/S04_SW_TX3_N: U1.BA23 (TXN[19]); also elsewhere on the board
/S04_SW_TX3_P: U1.BB23 (TXP[19]); also elsewhere on the board
/S05_SW_TX0_N: U1.AY22 (TXN[20]); also elsewhere on the board
/S05_SW_TX0_P: U1.BA22 (TXP[20]); also elsewhere on the board
/S05_SW_TX1_N: U1.BA21 (TXN[21]); also elsewhere on the board
/S05_SW_TX1_P: U1.BB21 (TXP[21]); also elsewhere on the board
/S05_SW_TX2_N: U1.AY20 (TXN[22]); also elsewhere on the board
/S05_SW_TX2_P: U1.BA20 (TXP[22]); also elsewhere on the board
/S05_SW_TX3_N: U1.BA19 (TXN[23]); also elsewhere on the board
/S05_SW_TX3_P: U1.BB19 (TXP[23]); also elsewhere on the board
/S06_SW_TX0_N: U1.AY18 (TXN[24]); also elsewhere on the board
/S06_SW_TX0_P: U1.BA18 (TXP[24]); also elsewhere on the board
/S06_SW_TX1_N: U1.BA17 (TXN[25]); also elsewhere on the board
/S06_SW_TX1_P: U1.BB17 (TXP[25]); also elsewhere on the board
/S06_SW_TX2_N: U1.AY16 (TXN[26]); also elsewhere on the board
/S06_SW_TX2_P: U1.BA16 (TXP[26]); also elsewhere on the board
/S06_SW_TX3_N: U1.BA15 (TXN[27]); also elsewhere on the board
/S06_SW_TX3_P: U1.BB15 (TXP[27]); also elsewhere on the board
/S07_SW_TX0_N: U1.AY14 (TXN[28]); also elsewhere on the board
/S07_SW_TX0_P: U1.BA14 (TXP[28]); also elsewhere on the board
/S07_SW_TX1_N: U1.BA13 (TXN[29]); also elsewhere on the board
/S07_SW_TX1_P: U1.BB13 (TXP[29]); also elsewhere on the board
/S07_SW_TX2_N: U1.AY12 (TXN[30]); also elsewhere on the board
/S07_SW_TX2_P: U1.BA12 (TXP[30]); also elsewhere on the board
/S07_SW_TX3_N: U1.BA11 (TXN[31]); also elsewhere on the board
/S07_SW_TX3_P: U1.BB11 (TXP[31]); also elsewhere on the board
/S08_SW_TX0_N: U1.AY10 (TXN[32]); also elsewhere on the board
/S08_SW_TX0_P: U1.BA10 (TXP[32]); also elsewhere on the board
/S08_SW_TX1_N: U1.BA9 (TXN[33]); also elsewhere on the board
/S08_SW_TX1_P: U1.BB9 (TXP[33]); also elsewhere on the board
/S08_SW_TX2_N: U1.AY8 (TXN[34]); also elsewhere on the board
/S08_SW_TX2_P: U1.BA8 (TXP[34]); also elsewhere on the board
/S08_SW_TX3_N: U1.BA7 (TXN[35]); also elsewhere on the board
/S08_SW_TX3_P: U1.BB7 (TXP[35]); also elsewhere on the board
/S09_SW_TX0_N: U1.AY6 (TXN[36]); also elsewhere on the board
/S09_SW_TX0_P: U1.BA6 (TXP[36]); also elsewhere on the board
/S09_SW_TX1_N: U1.BA5 (TXN[37]); also elsewhere on the board
/S09_SW_TX1_P: U1.BB5 (TXP[37]); also elsewhere on the board
/S09_SW_TX2_N: U1.AY4 (TXN[38]); also elsewhere on the board
/S09_SW_TX2_P: U1.BA4 (TXP[38]); also elsewhere on the board
/S09_SW_TX3_N: U1.BA3 (TXN[39]); also elsewhere on the board
/S09_SW_TX3_P: U1.BB3 (TXP[39]); also elsewhere on the board
/UP_RX0_N: U1.H26 (RXN[64]); also elsewhere on the board
/UP_RX0_P: U1.G26 (RXP[64]); also elsewhere on the board
/UP_RX1_N: U1.F25 (RXN[65]); also elsewhere on the board
/UP_RX1_P: U1.E25 (RXP[65]); also elsewhere on the board
/UP_RX2_N: U1.H24 (RXN[66]); also elsewhere on the board
/UP_RX2_P: U1.G24 (RXP[66]); also elsewhere on the board
/UP_RX3_N: U1.F23 (RXN[67]); also elsewhere on the board
/UP_RX3_P: U1.E23 (RXP[67]); also elsewhere on the board
/UP_TX0_N: U1.B26 (TXN[64]); also elsewhere on the board
/UP_TX1_N: U1.C25 (TXN[65]); also elsewhere on the board
/UP_TX1_P: U1.B25 (TXP[65]); also elsewhere on the board
/UP_TX2_N: U1.B24 (TXN[66]); also elsewhere on the board
/UP_TX3_N: U1.C23 (TXN[67]); also elsewhere on the board
/UP_TX3_P: U1.B23 (TXP[67]); also elsewhere on the board
